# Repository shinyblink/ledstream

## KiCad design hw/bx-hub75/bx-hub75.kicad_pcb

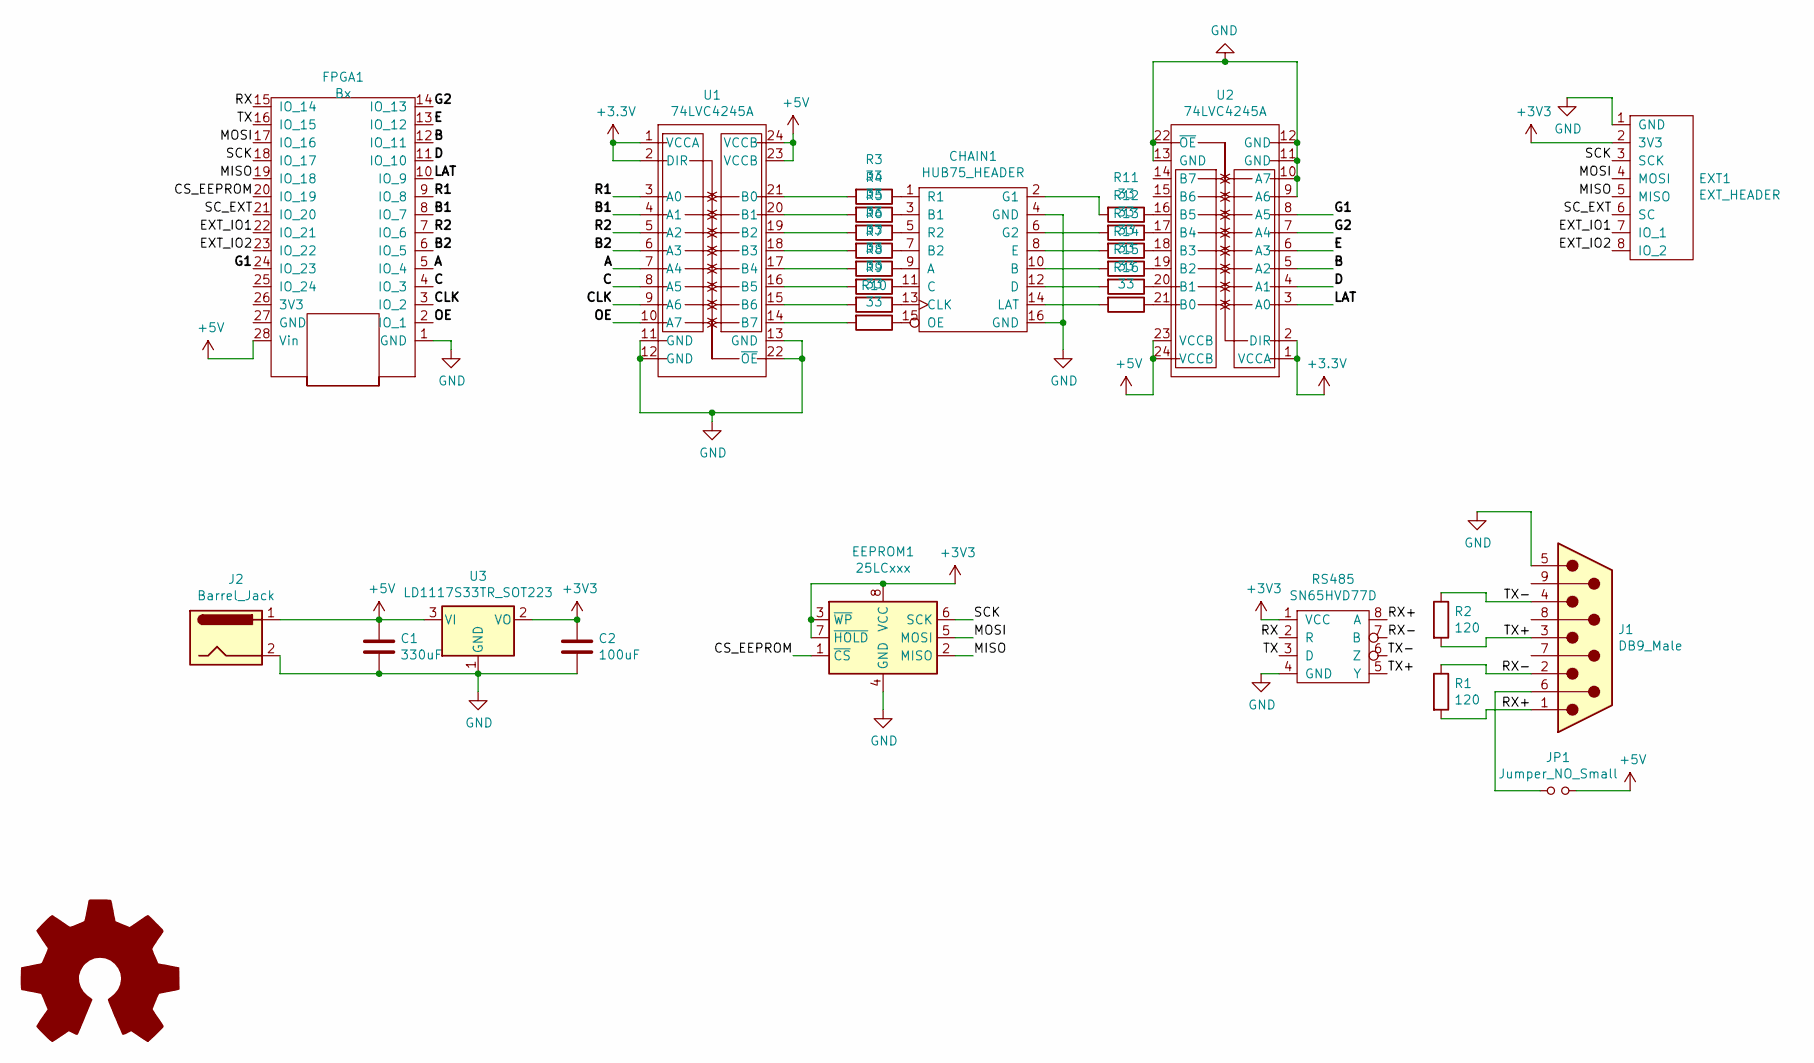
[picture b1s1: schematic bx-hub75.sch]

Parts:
C1: 330uF; CP_Elec_6.3x7.7
C2: 100uF; CP_Elec_5x5.4
CHAIN1: HUB75_HEADER; IDC-Header_2x08_P2.54mm_Vertical
EEPROM1: 25LCxxx; SOIC-8_3.9x4.9mm_P1.27mm
EXT1: EXT_HEADER; PinHeader_1x08_P2.54mm_Vertical
FPGA1: Bx; TinyFPGA_BX
J1: DB9_Male; DSUB-9_Male_Horizontal_P2.77x2.84mm_EdgePinOffset4.94mm_Hou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
J2: Barrel_Jack; BarrelJack_Wuerth_6941xx301002
JP1: Jumper_NO_Small; PinHeader_1x02_P2.54mm_Vertical
OSHW1: Logo_Open_Hardware_Large; OSHW-Logo2_9.8x8mm_SilkScreen
R1, R2: 120; R_1210_3225Metric_Pad1.42x2.65mm_HandSolder
R3, R4, R5, R6, R7, R8, R9, R10, R11, R12, R13, R14, R15, R16: 33; R_0805_2012Metric_Pad1.15x1.40mm_HandSolder
RS485: SN65HVD77D; SOIC-8_3.9x4.9mm_P1.27mm
U1, U2: 74LVC4245A; SOIC-24W_7.5x15.4mm_P1.27mm
U3: LD1117S33TR_SOT223; SOT-223-3_TabPin2

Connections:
+5V: C1.1, FPGA1.28 (Vin), J2.1, JP1.2, U1.23 (VCCB), U1.24 (VCCB), U2.23 (VCCB), U2.24 (VCCB), U3.3 (VI)
/A: FPGA1.5 (IO_4), U1.7 (A4)
/B: FPGA1.12 (IO_11), U2.5 (A2)
/B1: FPGA1.8 (IO_7), U1.4 (A1)
/B2: FPGA1.6 (IO_5), U1.6 (A3)
/C: FPGA1.4 (IO_3), U1.8 (A5)
/CLK: FPGA1.3 (IO_2), U1.9 (A6)
/CS_EEPROM: EEPROM1.1 (~CS), FPGA1.20 (IO_19)
/D: FPGA1.11 (IO_10), U2.4 (A1)
/E: FPGA1.13 (IO_12), U2.6 (A3)
/EXT_IO1: EXT1.7 (IO_1), FPGA1.22 (IO_21)
/EXT_IO2: EXT1.8 (IO_2), FPGA1.23 (IO_22)
/G1: FPGA1.24 (IO_23), U2.8 (A5)
/G2: FPGA1.14 (IO_13), U2.7 (A4)
/LAT: FPGA1.10 (IO_9), U2.3 (A0)
/MISO: EEPROM1.2 (MISO), EXT1.5 (MISO), FPGA1.19 (IO_18)
/MOSI: EEPROM1.5 (MOSI), EXT1.4 (MOSI), FPGA1.17 (IO_16)
/OE: FPGA1.2 (IO_1), U1.10 (A7)
/R1: FPGA1.9 (IO_8), U1.3 (A0)
/R2: FPGA1.7 (IO_6), U1.5 (A2)
/RX: FPGA1.15 (IO_14), RS485.2 (R)
/RX+: J1.1, R1.2, RS485.8 (A)
/RX-: J1.2, R1.1, RS485.7 (B)
/SCK: EEPROM1.6 (SCK), EXT1.3 (SCK), FPGA1.18 (IO_17)
/SC_EXT: EXT1.6 (SC), FPGA1.21 (IO_20)
/TX: FPGA1.16 (IO_15), RS485.3 (D)
/TX+: J1.3, R2.2, RS485.5 (Y)
/TX-: J1.4, R2.1, RS485.6 (Z)
GND: C1.2, C2.2, CHAIN1.4 (GND), CHAIN1.16 (GND), EEPROM1.4 (GND), EXT1.1 (GND), FPGA1.1 (GND), J1.5, J2.2, RS485.4 (GND), U1.11 (GND), U1.12 (GND), U1.13 (GND), U1.22 (~OE), U2.9 (A6), U2.10 (A7), U2.11 (GND), U2.12 (GND), U2.13 (GND), U2.22 (~OE), U3.1 (GND)
unnamed: CHAIN1.1 (R1), R3.1
unnamed: CHAIN1.2 (G1), R11.2
unnamed: CHAIN1.3 (B1), R4.1
unnamed: CHAIN1.5 (R2), R5.1
unnamed: CHAIN1.6 (G2), R12.2
unnamed: CHAIN1.7 (B2), R6.1
unnamed: CHAIN1.8 (E), R13.2
unnamed: CHAIN1.9 (A), R7.1
unnamed: CHAIN1.10 (B), R14.2
unnamed: CHAIN1.11 (C), R8.1
unnamed: CHAIN1.12 (D), R15.2
unnamed: CHAIN1.13 (CLK), R9.1
unnamed: CHAIN1.14 (LAT), R16.2
unnamed: CHAIN1.15 (OE), R10.1
unnamed: J1.6, JP1.1
unnamed: R3.2, U1.21 (B0)
unnamed: R4.2, U1.20 (B1)
unnamed: R5.2, U1.19 (B2)
unnamed: R6.2, U1.18 (B3)
unnamed: R7.2, U1.17 (B4)
unnamed: R8.2, U1.16 (B5)
unnamed: R9.2, U1.15 (B6)
unnamed: R10.2, U1.14 (B7)
unnamed: R11.1, U2.16 (B5)
unnamed: R12.1, U2.17 (B4)
unnamed: R13.1, U2.18 (B3)
unnamed: R14.1, U2.19 (B2)
unnamed: R15.1, U2.20 (B1)
unnamed: R16.1, U2.21 (B0)

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
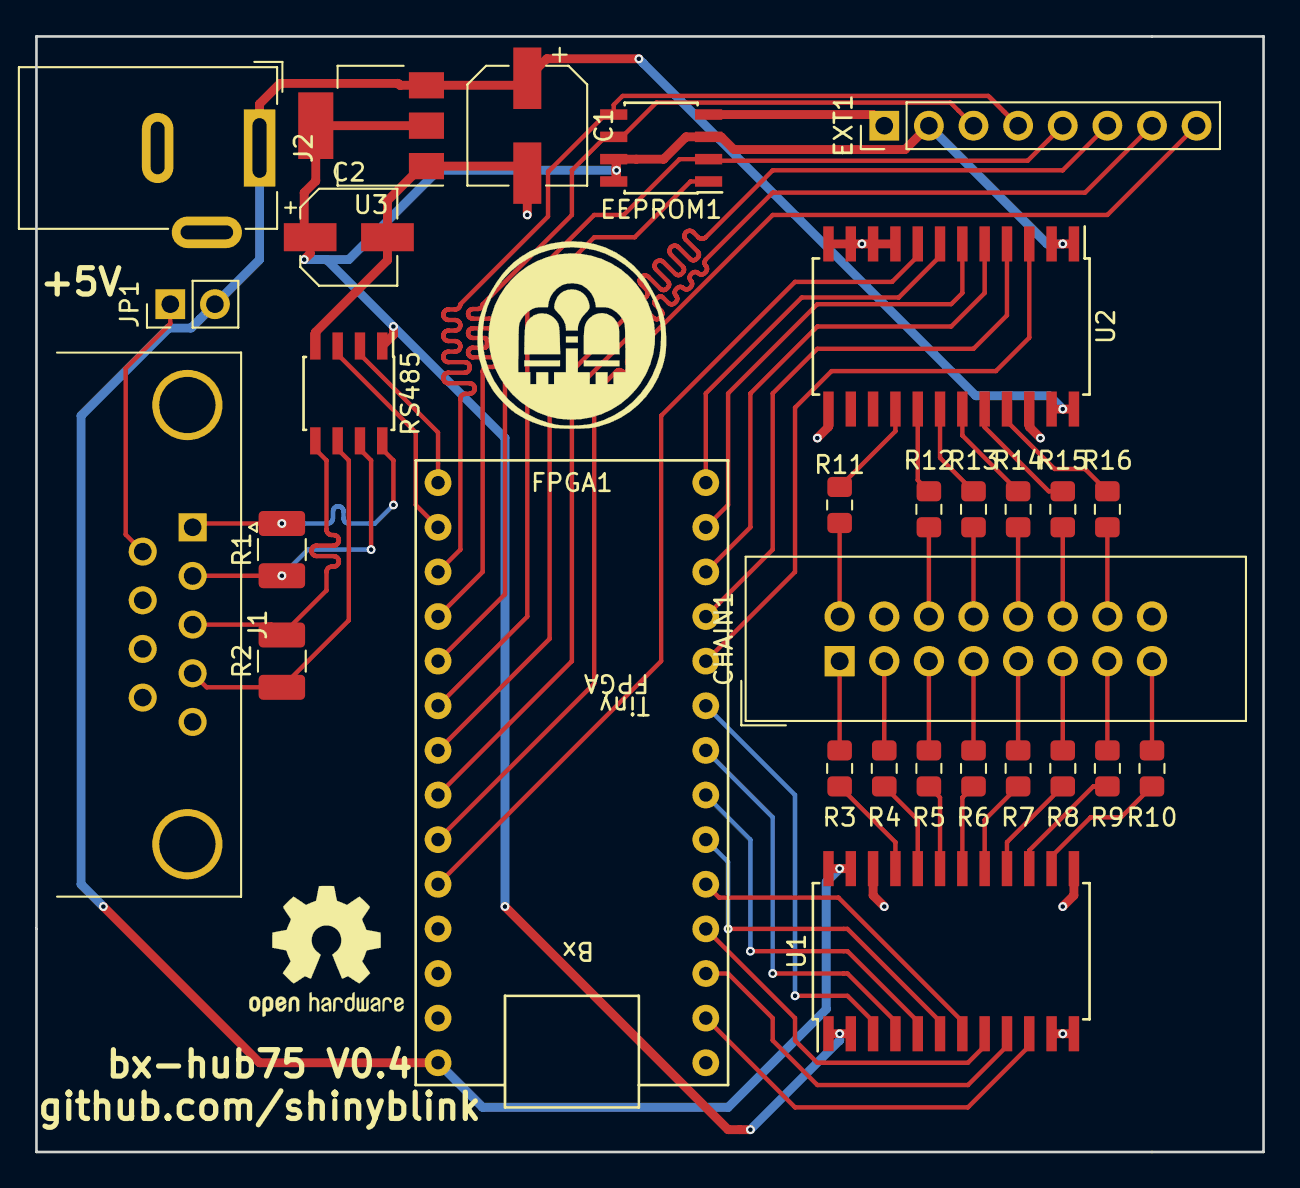
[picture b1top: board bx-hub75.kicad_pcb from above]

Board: 2 copper layers, 69.8 x 63.5 mm, 30 parts (0 on the bottom side), 59 nets.

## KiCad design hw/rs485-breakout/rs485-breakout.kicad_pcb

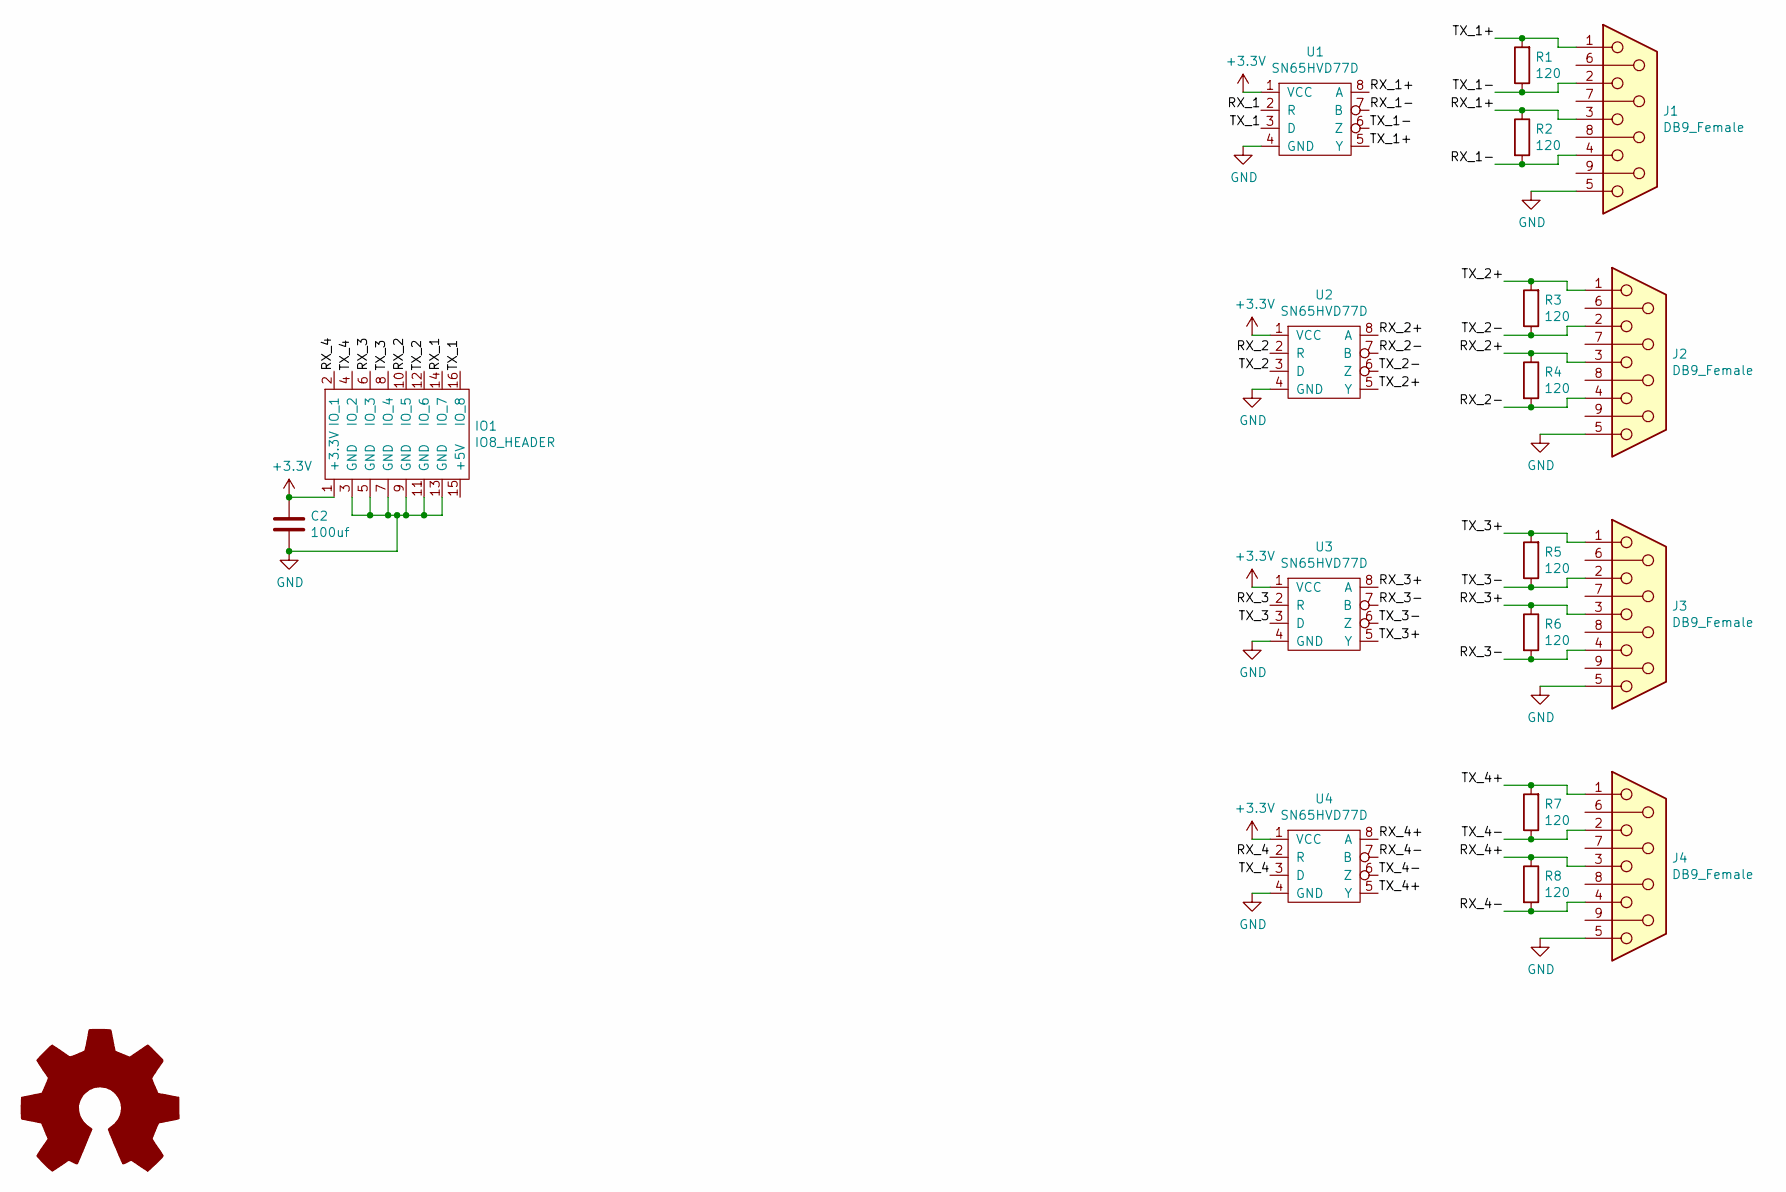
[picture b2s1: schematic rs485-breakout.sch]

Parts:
C2: 100uf; CP_Elec_5x5.4
IO1: IO8_HEADER; IDC-Header_2x08_P2.54mm_Vertical
J1, J2, J3, J4: DB9_Female; DSUB-9_Female_Horizontal_P2.77x2.84mm_EdgePinOffset7.70mm_H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
R1, R2, R3, R4, R5, R6, R7, R8: 120; R_1210_3225Metric_Pad1.42x2.65mm_HandSolder
U1, U2, U3, U4: SN65HVD77D; SOIC-8_3.9x4.9mm_P1.27mm

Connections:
+3V3: C2.1, IO1.1 (+3.3V), U1.1 (VCC), U2.1 (VCC), U3.1 (VCC), U4.1 (VCC)
/RX_1: IO1.14 (IO_7), U1.2 (R)
/RX_1+: J1.3, R2.1, U1.8 (A)
/RX_1-: J1.4, R2.2, U1.7 (B)
/RX_2: IO1.10 (IO_5), U2.2 (R)
/RX_2+: J2.3, R4.1, U2.8 (A)
/RX_2-: J2.4, R4.2, U2.7 (B)
/RX_3: IO1.6 (IO_3), U3.2 (R)
/RX_3+: J3.3, R6.1, U3.8 (A)
/RX_3-: J3.4, R6.2, U3.7 (B)
/RX_4: IO1.2 (IO_1), U4.2 (R)
/RX_4+: J4.3, R8.1, U4.8 (A)
/RX_4-: J4.4, R8.2, U4.7 (B)
/TX_1: IO1.16 (IO_8), U1.3 (D)
/TX_1+: J1.1, R1.2, U1.5 (Y)
/TX_1-: J1.2, R1.1, U1.6 (Z)
/TX_2: IO1.12 (IO_6), U2.3 (D)
/TX_2+: J2.1, R3.2, U2.5 (Y)
/TX_2-: J2.2, R3.1, U2.6 (Z)
/TX_3: IO1.8 (IO_4), U3.3 (D)
/TX_3+: J3.1, R5.2, U3.5 (Y)
/TX_3-: J3.2, R5.1, U3.6 (Z)
/TX_4: IO1.4 (IO_2), U4.3 (D)
/TX_4+: J4.1, R7.2, U4.5 (Y)
/TX_4-: J4.2, R7.1, U4.6 (Z)
GND: C2.2, IO1.3 (GND), IO1.5 (GND), IO1.7 (GND), IO1.9 (GND), IO1.11 (GND), IO1.13 (GND), J1.5, J2.5, J3.5, J4.5, U1.4 (GND), U2.4 (GND), U3.4 (GND), U4.4 (GND)

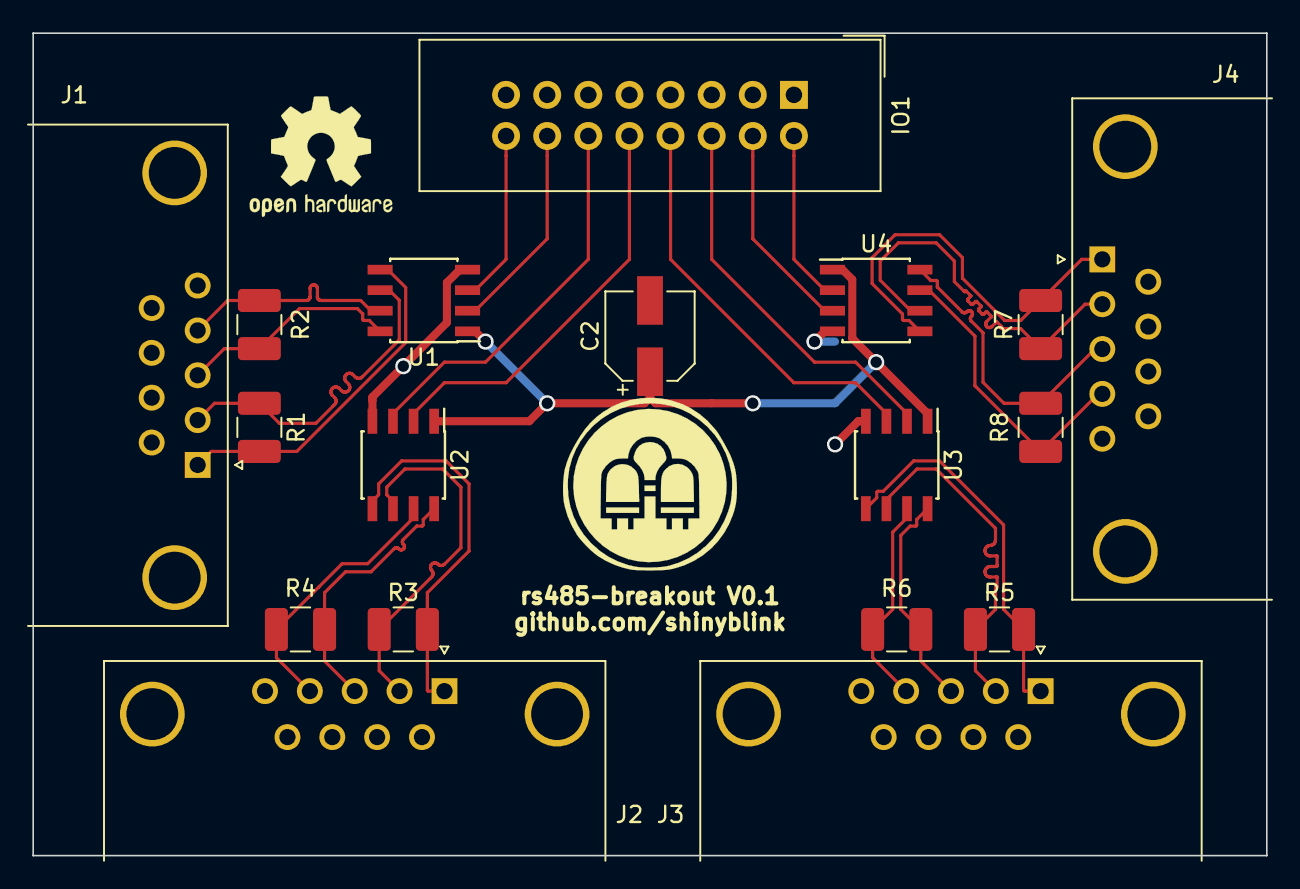
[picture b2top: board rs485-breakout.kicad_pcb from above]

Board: 2 copper layers, 76.2 x 50.8 mm, 18 parts (0 on the bottom side), 26 nets.

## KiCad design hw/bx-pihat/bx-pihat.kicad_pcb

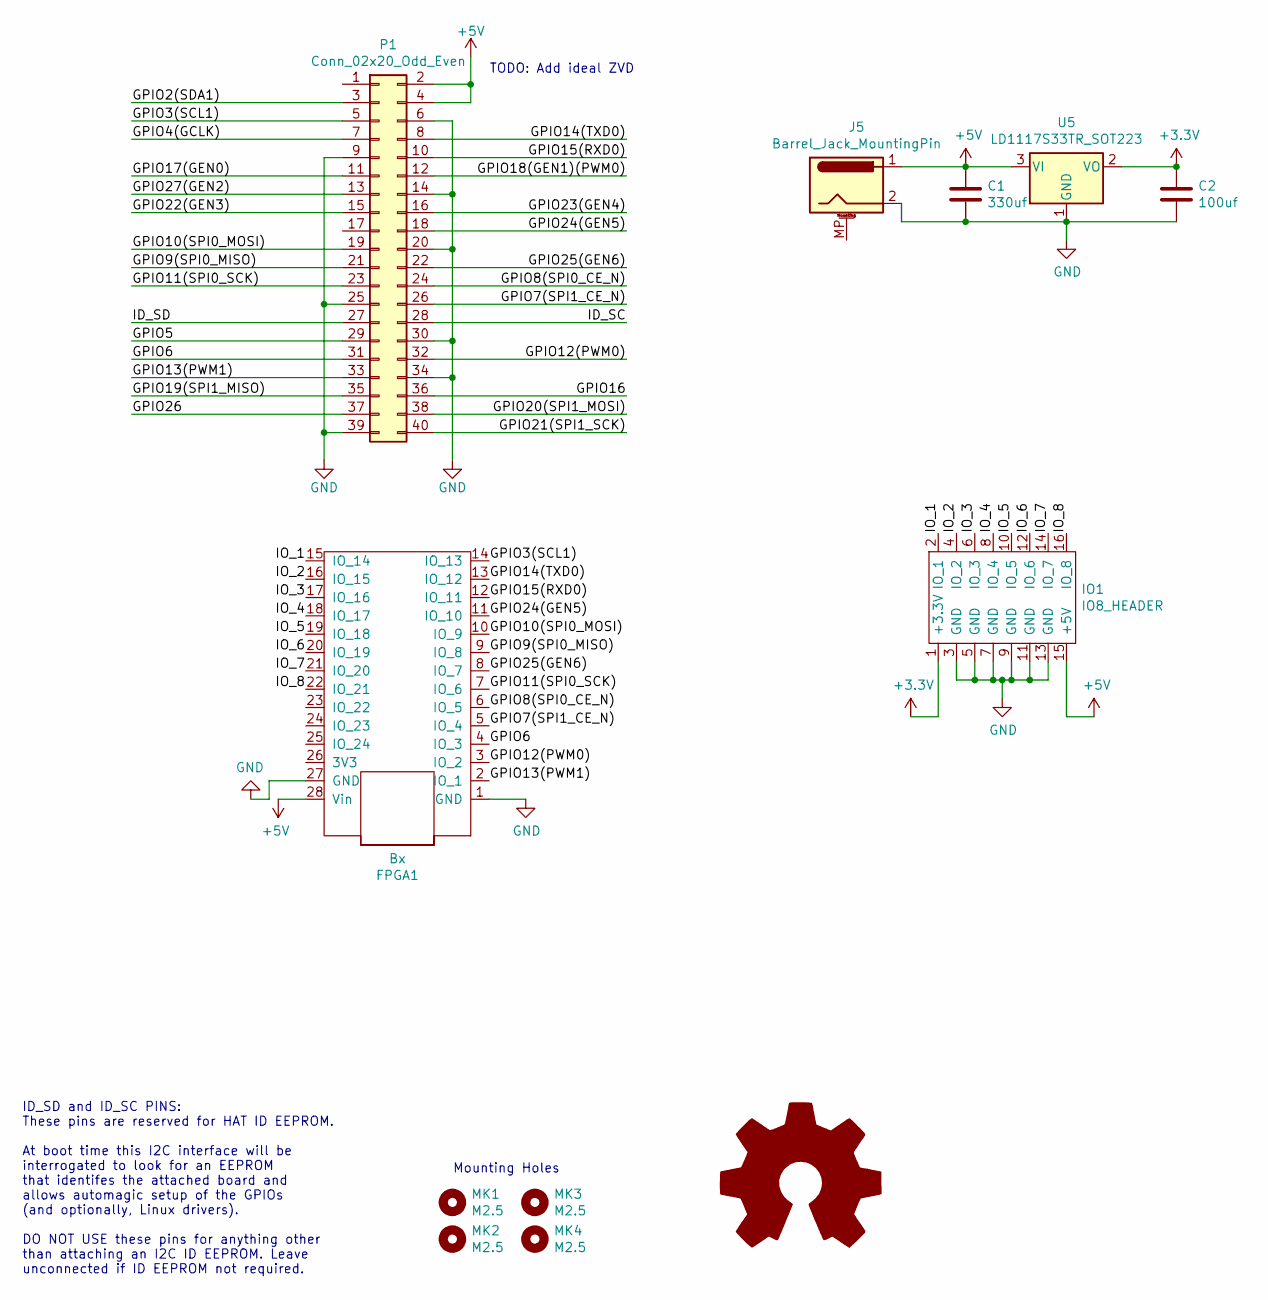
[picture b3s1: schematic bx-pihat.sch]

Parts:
C1: 330uf; CP_Elec_6.3x7.7
C2: 100uf; CP_Elec_5x5.4
FPGA1: Bx; TinyFPGA_BX
IO1: IO8_HEADER; IDC-Header_2x08_P2.54mm_Vertical
J5: Barrel_Jack_MountingPin; BarrelJack_Wuerth_6941xx301002
MK1, MK2, MK3, MK4: M2.5; MountingHole_2.7mm_M2.5
P1: Conn_02x20_Odd_Even; PinSocket_2x20_P2.54mm_Vertical
U5: LD1117S33TR_SOT223; SOT-223-3_TabPin2

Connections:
+3V3: C2.1, IO1.1 (+3.3V), U5.2 (VO)
+5V: C1.1, FPGA1.28 (Vin), IO1.15 (+5V), J5.1, P1.2, P1.4, U5.3 (VI)
/GPIO2(SDA1): P1.3
/GPIO3(SCL1): FPGA1.14 (IO_13), P1.5
/GPIO4(GCLK): P1.7
/GPIO5: P1.29
/GPIO6: FPGA1.4 (IO_3), P1.31
/GPIO7(SPI1_CE_N): FPGA1.5 (IO_4), P1.26
/GPIO8(SPI0_CE_N): FPGA1.6 (IO_5), P1.24
/GPIO9(SPI0_MISO): FPGA1.9 (IO_8), P1.21
/GPIO10(SPI0_MOSI): FPGA1.10 (IO_9), P1.19
/GPIO11(SPI0_SCK): FPGA1.7 (IO_6), P1.23
/GPIO12(PWM0): FPGA1.3 (IO_2), P1.32
/GPIO13(PWM1): FPGA1.2 (IO_1), P1.33
/GPIO14(TXD0): FPGA1.13 (IO_12), P1.8
/GPIO15(RXD0): FPGA1.12 (IO_11), P1.10
/GPIO16: P1.36
/GPIO17(GEN0): P1.11
/GPIO18(GEN1)(PWM0): P1.12
/GPIO19(SPI1_MISO): P1.35
/GPIO20(SPI1_MOSI): P1.38
/GPIO21(SPI1_SCK): P1.40
/GPIO22(GEN3): P1.15
/GPIO23(GEN4): P1.16
/GPIO24(GEN5): FPGA1.11 (IO_10), P1.18
/GPIO25(GEN6): FPGA1.8 (IO_7), P1.22
/GPIO26: P1.37
/GPIO27(GEN2): P1.13
/ID_SC: P1.28
/ID_SD: P1.27
/IO_1: FPGA1.15 (IO_14), IO1.2 (IO_1)
/IO_2: FPGA1.16 (IO_15), IO1.4 (IO_2)
/IO_3: FPGA1.17 (IO_16), IO1.6 (IO_3)
/IO_4: FPGA1.18 (IO_17), IO1.8 (IO_4)
/IO_5: FPGA1.19 (IO_18), IO1.10 (IO_5)
/IO_6: FPGA1.20 (IO_19), IO1.12 (IO_6)
/IO_7: FPGA1.21 (IO_20), IO1.14 (IO_7)
/IO_8: FPGA1.22 (IO_21), IO1.16 (IO_8)
GND: C1.2, C2.2, FPGA1.1 (GND), FPGA1.27 (GND), IO1.3 (GND), IO1.5 (GND), IO1.7 (GND), IO1.9 (GND), IO1.11 (GND), IO1.13 (GND), J5.2, P1.6, P1.9, P1.14, P1.20, P1.25, P1.30, P1.34, P1.39, U5.1 (GND)

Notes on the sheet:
ID_SD and ID_SC PINS: These pins are reserved for HAT ID EEPROM. At boot time this I2C interface will be interrogated to look for an EEPROM that identifes the attached board and allows automagic setup of the GPIOs (and optionally, Linux drivers). DO NOT USE these pins for anything other than attach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
Mounting Holes
TODO: Add ideal ZVD

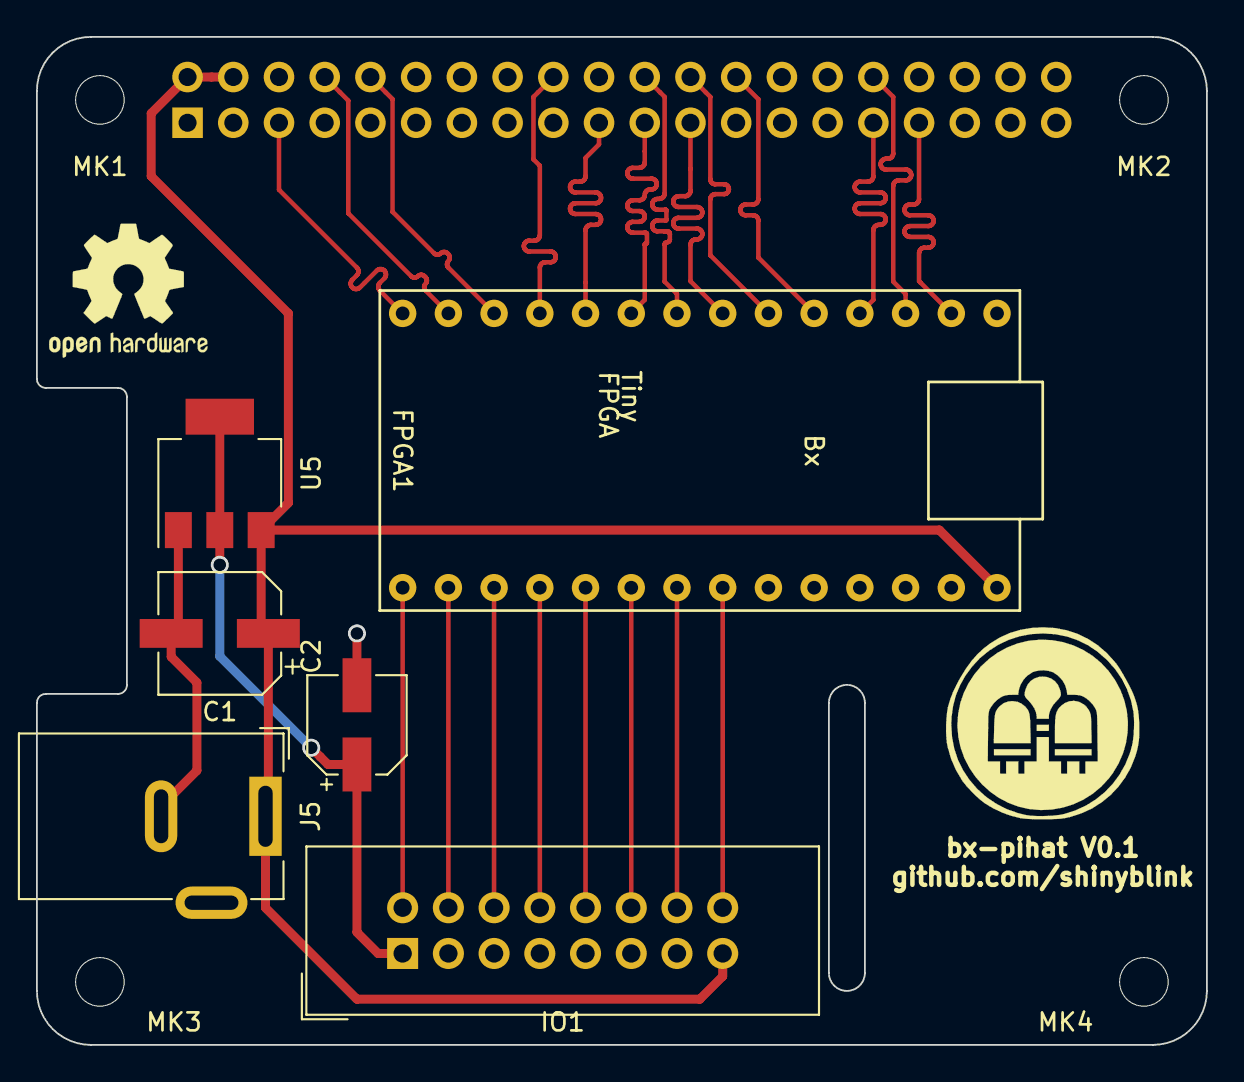
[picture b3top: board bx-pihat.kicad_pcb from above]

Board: 2 copper layers, 65.0 x 56.0 mm, 11 parts (1 on the bottom side), 24 nets.

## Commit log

2018-11-14 Epoch.
    It all starts with a single footprint. And a symbol.
2018-11-14 hw/bx-hub75: hook up HUB75 to line drivers.
2018-11-15 hw/bx-hub75: hook up RS485 and line drivers to FPGA.
2018-11-18 hw/bx-hub75: 3.3V VREG
2018-11-19 hw/bx-hub75: add SPI eeprom/decoupling caps
2018-11-19 hw/bx-hub75: Initial PCB layout.
    God, routing this is complex.
2018-11-19 hw/bx-hub75: 74HCT244 -> 74HCT541
2018-11-20 hw/bx-hub75: finish basic routing.
2018-11-21 hw/{library,bx-hub75}: TinyFPGA has 28 pins, not 26...
2018-11-26 hw/bx-hub75: oshw logo, text, extension header
2018-11-26 hw/bx-hub75: add barrel jack
2018-11-29 hw: Add gerber generation script/Makefile
2018-11-29 hw/bx-hub75: reroute to 0.1m minimum trace spacing
2018-12-01 hw/bx-hub75: allow bom generation with kibom
2018-12-07 hw/bx-hub75: fab changes.
2018-12-07 hw/bx-hub75: V0.2 PCB/SCH.
2018-12-10 hw/bx-hub75: v0.3, E Line support.
2018-12-13 sw/bx-smitest: Add Verilog Raspberry PI SMI driver.
    Probably not working, but it's a start.
2018-12-13 fix makefile for nextpnr
2018-12-13 sw/bx-smitest: 64MHz PLL.
2018-12-13 sw/bx-smitest: try to get smi working
2018-12-13 sw/bx-smitest: fix asynchronous OE/WE not always registering
2018-12-16 sw/*: WIP HUB75 driver.
    In theory, this does 1bit output on HUB75 panels, with N cycles of latency inbetween. Many thanks to @kbob for his code, from which I took a lot of inspiration.
2018-12-16 sw/*: Add ETC1 decoder.
    Comes with rudimentary testing.
2018-12-16 sw/etc1: improve testbench, fix wrong bit width of etc1_decode x/y inputs
2018-12-16 sw/bx-hub75test: add hub75 testing, its broken.
2018-12-16 sw/bx-hub75test: wire order?
2018-12-17 sw/bx-hub75test: fix more issues.
2018-12-17 sw/bx-hub75test: Fix typos. Thanks @gregdavill.
    I was looking at hub75_driver the whole time, thank you.
2018-12-22 hw/bx-pihat: add v0.1.
2018-12-22 hw/rs485-breakout: add V0.1
2018-12-22 hw/bx-hub75: release V0.4.
